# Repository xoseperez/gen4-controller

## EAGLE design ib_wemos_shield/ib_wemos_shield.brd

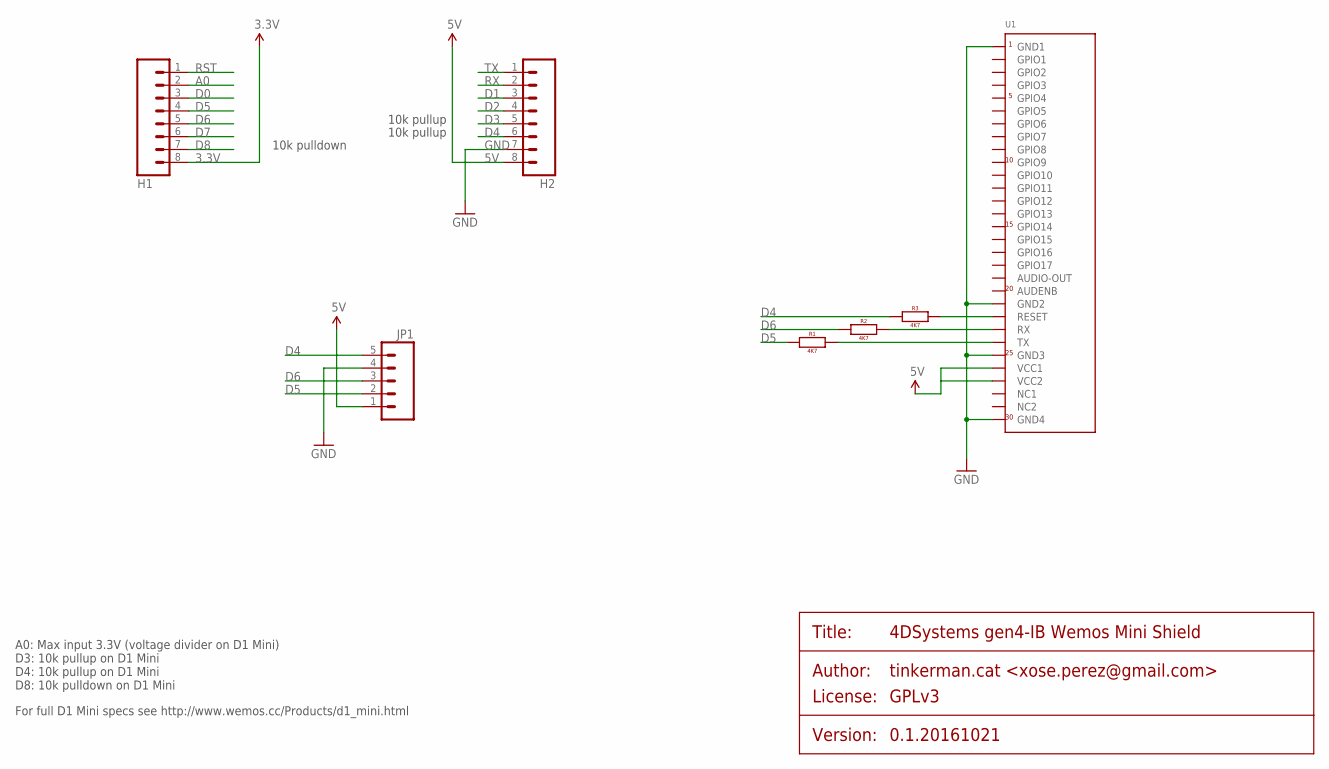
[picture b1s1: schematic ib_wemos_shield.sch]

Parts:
H1, H2: M08; 1X08_NO_SILK
JP1: M05PTH; 1X05
R1, R2, R3: 4K7; 0805
U1: 4DSYSTEMS-GEN4-INTERFACETOP; FPC_XF2M-3015-1A

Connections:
3.3V: H1.8
5V: H2.8, JP1.1, U1.26 (VCC1), U1.27 (VCC2)
A0: H1.2
D0: H1.3
D1: H2.3
D2: H2.4
D3: H2.5
D4: H2.6, JP1.5, R3.1
D5: H1.4, JP1.2, R1.1
D6: H1.5, JP1.3, R2.1
D7: H1.6
D8: H1.7
GND: H2.7, JP1.4, U1.1 (GND1), U1.21 (GND2), U1.25 (GND3), U1.30 (GND4)
GPIO1: U1.2 (GPIO1)
GPIO2: U1.3 (GPIO2)
GPIO3: U1.4 (GPIO3)
unnamed: R1.2, U1.24 (TX)
unnamed: R2.2, U1.23 (RX)
unnamed: R3.2, U1.22 (RESET)
NC1: U1.28 (NC1)
RST: H1.1
RX: H2.2
TX: H2.1

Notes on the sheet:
A0: Max input 3.3V (voltage divider on D1 Mini) D3: 10k pullup on D1 Mini D4: 10k pullup on D1 Mini D8: 10k pulldown on D1 Mini
10k pulldown
10k pullup
For full D1 Mini specs see http://www.wemos.cc/Products/d1_mini.html

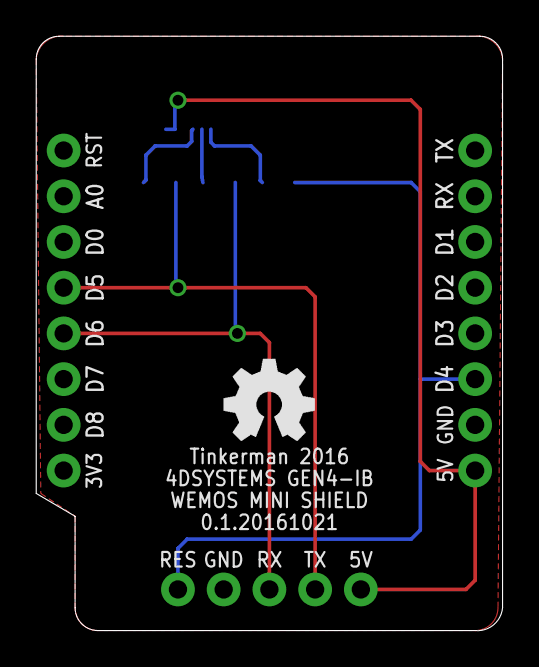
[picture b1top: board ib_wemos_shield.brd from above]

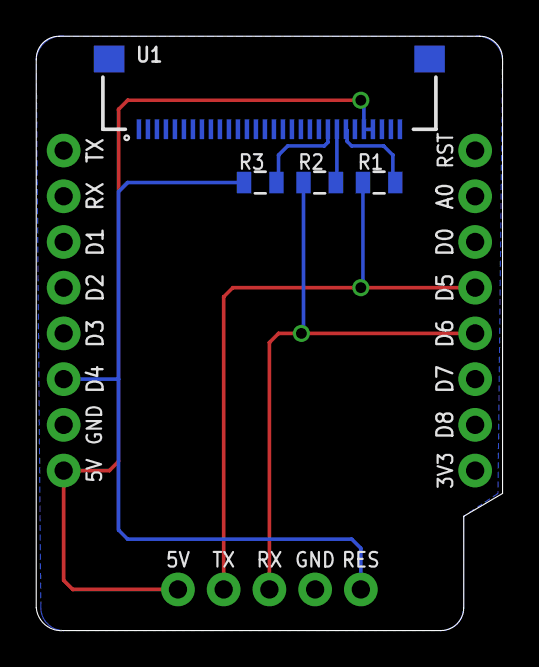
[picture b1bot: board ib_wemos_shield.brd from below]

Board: 2 copper layers, 25.9 x 33.0 mm, 7 parts (4 on the bottom side), 8 nets.

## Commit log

2016-10-21 Wemos mini shield

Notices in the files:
ib_wemos_shield/ib_wemos_shield.sch:
PROJECT_LICENSE: GPLv3
parts and their libraries:
freetronics-original: Licensing: CC v3.0 Share-Alike You are welcome to use this library for commercial purposes.
